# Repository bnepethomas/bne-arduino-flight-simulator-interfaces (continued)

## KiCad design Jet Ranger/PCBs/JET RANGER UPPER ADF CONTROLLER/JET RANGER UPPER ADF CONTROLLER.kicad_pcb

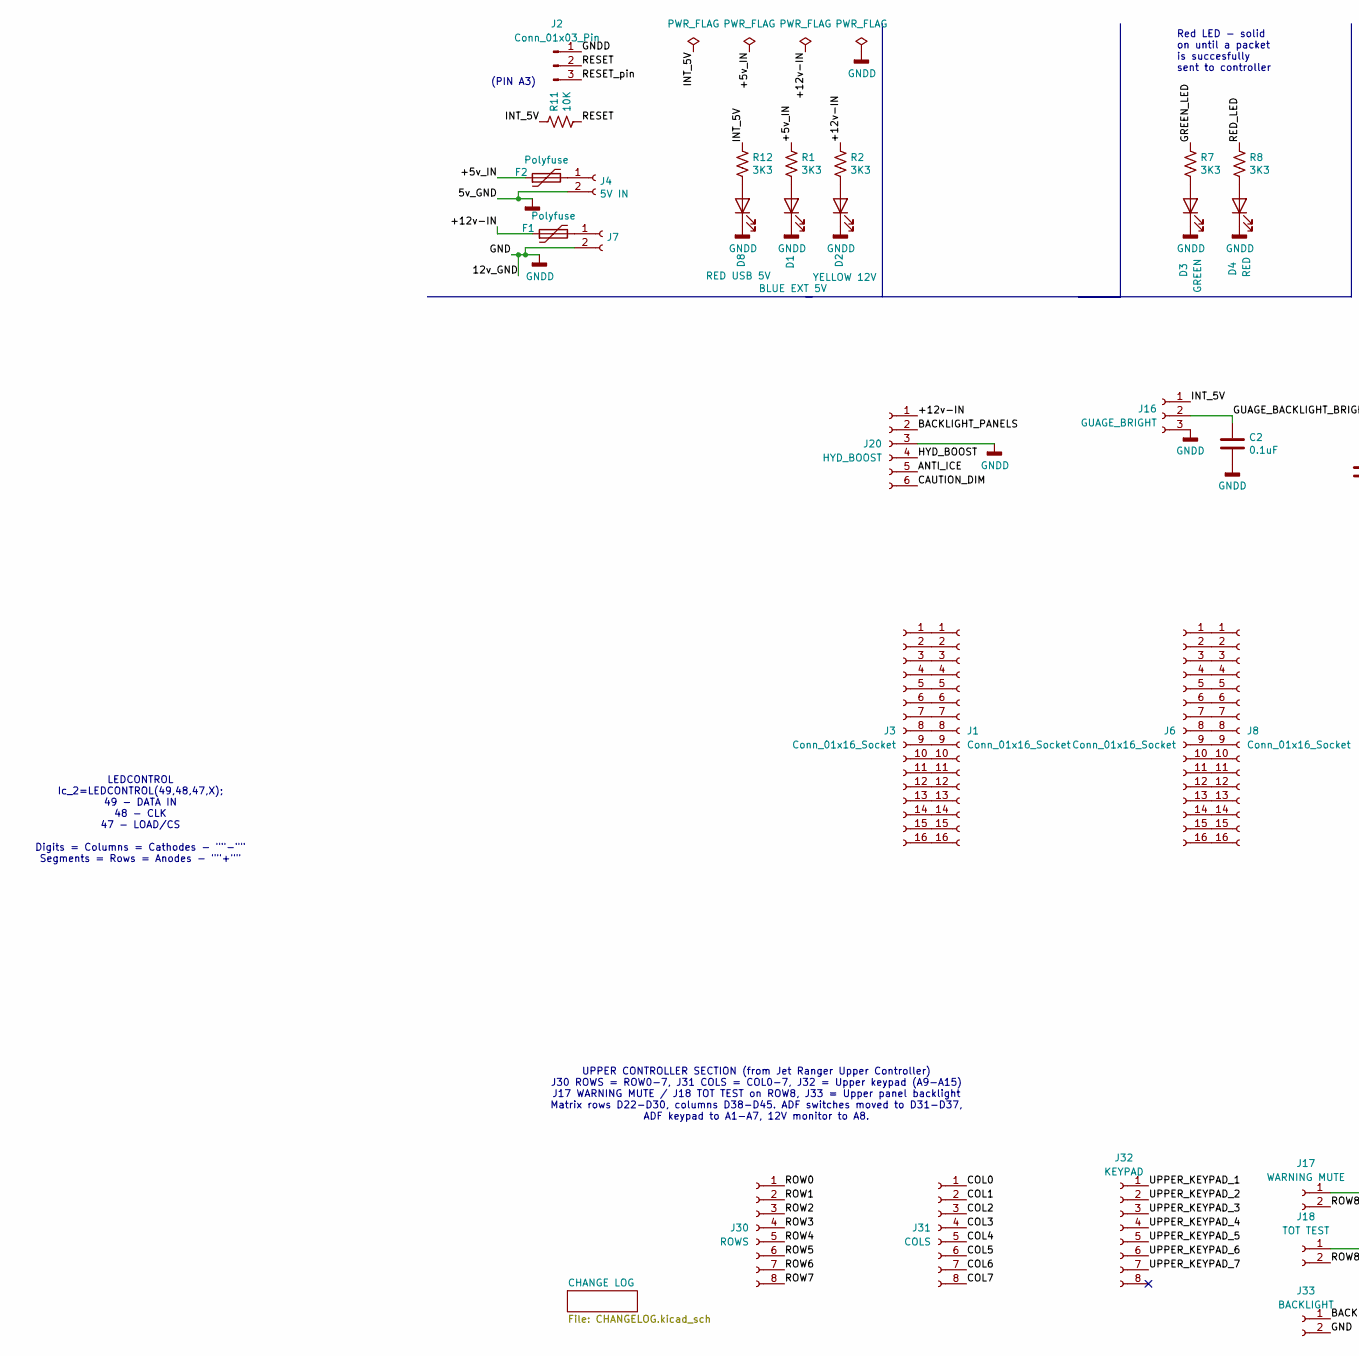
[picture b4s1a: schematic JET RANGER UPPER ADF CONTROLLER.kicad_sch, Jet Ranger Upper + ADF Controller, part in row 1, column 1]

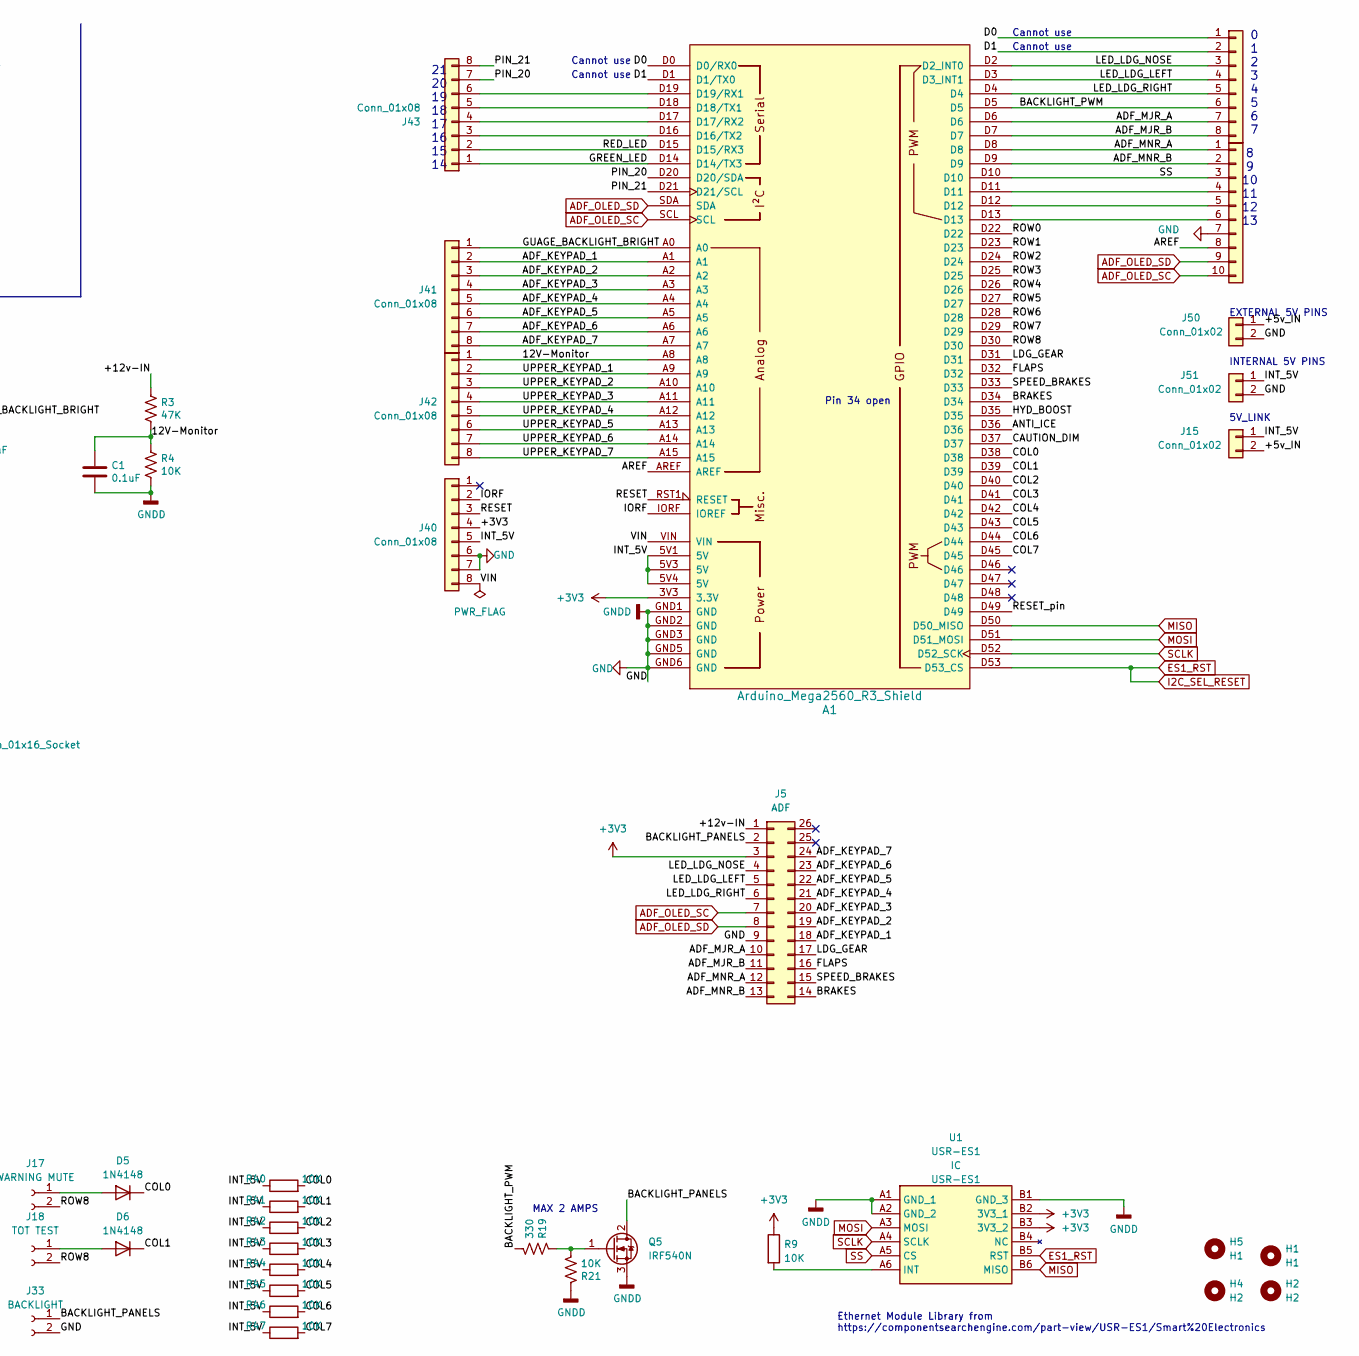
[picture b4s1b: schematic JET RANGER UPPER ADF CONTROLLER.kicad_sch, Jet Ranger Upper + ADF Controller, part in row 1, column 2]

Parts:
A1: Arduino_Mega2560_R3_Shield
C1, C2: 0.1uF; C_Disc_D6.0mm_W2.5mm_P5.00mm
D1: BLUE EXT 5V; LED_D3.0mm
D2: YELLOW 12V; LED_D3.0mm
D3: GREEN; LED_D3.0mm
D4: RED; LED_D3.0mm
D5, D6: 1N4148; D_DO-35_SOD27_P7.62mm_Horizontal
D8: RED USB 5V; LED_D3.0mm
F1, F2: Polyfuse; Fuse_Littelfuse_395Series
H1, H5: H1; MountingHole_3.2mm_M3
H2, H4: H2; MountingHole_3.2mm_M3
J1, J3, J6, J8: Conn_01x16_Socket; PinHeader_1x16_P2.54mm_Vertical
J2: Conn_01x03_Pin; PinHeader_1x03_P2.54mm_Vertical
J4: 5V IN; BarrelJack_Horizontal
J5: ADF; IDC-Header_2x13_P2.54mm_Vertical
J7: STEPPER IN 12-20VDC; BarrelJack_Horizontal
J15, J50, J51: Conn_01x02; PinHeader_1x02_P2.54mm_Vertical
J16: GUAGE_BRIGHT; Molex_KK-254_AE-6410-03A_1x03_P2.54mm_Vertical
J17: WARNING MUTE; Molex_KK-254_AE-6410-02A_1x02_P2.54mm_Vertical
J18: TOT TEST; Molex_KK-254_AE-6410-02A_1x02_P2.54mm_Vertical
J20: HYD_BOOST; Molex_KK-254_AE-6410-06A_1x06_P2.54mm_Vertical
J30: ROWS; Molex_KK-254_AE-6410-08A_1x08_P2.54mm_Vertical
J31: COLS; Molex_KK-254_AE-6410-08A_1x08_P2.54mm_Vertical
J32: KEYPAD; Molex_KK-254_AE-6410-08A_1x08_P2.54mm_Vertical
J33: BACKLIGHT; Molex_KK-254_AE-6410-02A_1x02_P2.54mm_Vertical
J40, J41, J42, J43, J44: Conn_01x08; PinHeader_1x08_P2.54mm_Vertical
J45: Conn_01x10; PinHeader_1x10_P2.54mm_Vertical
Q5: IRF540N; TO-220-3_Vertical
R1, R2, R7, R8, R12: 3K3; R_Axial_DIN0207_L6.3mm_D2.5mm_P2.54mm_Vertical
R3: 47K; R_Axial_DIN0207_L6.3mm_D2.5mm_P2.54mm_Vertical
R4, R9, R11, R21, R40, R41, R42, R43, R44, R45, R46, R47: 10K; R_Axial_DIN0207_L6.3mm_D2.5mm_P2.54mm_Vertical
R19: 330; R_Axial_DIN0207_L6.3mm_D2.5mm_P2.54mm_Vertical
U1: USR-ES1; USRES1; Manufacturer_Part_Number USR-ES1

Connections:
+3V3: A1.3V3 (3.3V), J5.3, J40.4, R9.1, U1.B2 (3V3_1), U1.B3 (3V3_2)
/12V-Monitor: A1.A8, C1.1, J42.1, R3.2, R4.1
/+5v_IN: F2.1, J15.2, J50.1, R1.1
/+12v-IN: F1.1, J5.1, J20.1, R2.1, R3.1
/ADF_KEYPAD_1: A1.A1, J5.18, J41.2
/ADF_KEYPAD_2: A1.A2, J5.19, J41.3
/ADF_KEYPAD_3: A1.A3, J5.20, J41.4
/ADF_KEYPAD_4: A1.A4, J5.21, J41.5
/ADF_KEYPAD_5: A1.A5, J5.22, J41.6
/ADF_KEYPAD_6: A1.A6, J5.23, J41.7
/ADF_KEYPAD_7: A1.A7, J5.24, J41.8
/ADF_MJR_A: A1.D6, J5.10, J44.7
/ADF_MJR_B: A1.D7, J5.11, J44.8
/ADF_MNR_A: A1.D8, J5.12, J45.1
/ADF_MNR_B: A1.D9, J5.13, J45.2
/ANTI_ICE: A1.D36, J20.5
/AREF: A1.AREF, J45.8
/BACKLIGHT_PANELS: J5.2, J20.2, J33.1, Q5.2 (D)
/BACKLIGHT_PWM: A1.D5, J44.6, R19.2
/BRAKES: A1.D34, J5.14
/CAUTION_DIM: A1.D37, J20.6
/COL0: A1.D38, D5.1 (K), J31.1, R40.2
/COL1: A1.D39, D6.1 (K), J31.2, R41.2
/COL2: A1.D40, J31.3, R42.2
/COL3: A1.D41, J31.4, R43.2
/COL4: A1.D42, J31.5, R44.2
/COL5: A1.D43, J31.6, R45.2
/COL6: A1.D44, J31.7, R46.2
/COL7: A1.D45, J31.8, R47.2
/D0: A1.D0 (D0/RX0), J44.1
/D1: A1.D1 (D1/TX0), J44.2
/FLAPS: A1.D32, J5.16
/GREEN_LED: A1.D14 (D14/TX3), J43.1, R7.1
/GUAGE_BACKLIGHT_BRIGHT: A1.A0, C2.1, J16.2, J41.1
/HYD_BOOST: A1.D35, J20.4
/INT_5V: A1.5V1 (5V), A1.5V3 (5V), A1.5V4 (5V), J15.1, J16.1, J40.5, J51.1, R11.1, R12.1, R40.1, R41.1, R42.1, R43.1, R44.1, R45.1, R46.1, R47.1
/IORF: A1.IORF (IOREF), J40.2
/LDG_GEAR: A1.D31, J5.17
/LED_LDG_LEFT: A1.D3 (D3_INT1), J5.5, J44.4
/LED_LDG_NOSE: A1.D2 (D2_INT0), J5.4, J44.3
/LED_LDG_RIGHT: A1.D4, J5.6, J44.5
/PIN_20: A1.D20 (D20/SDA), J43.7
/PIN_21: A1.D21 (D21/SCL), J43.8
/RED_LED: A1.D15 (D15/RX3), J43.2, R8.1
/RESET: A1.RST1 (RESET), J2.2, J40.3, R11.2
/RESET_pin: A1.D49, J2.3
/ROW0: A1.D22, J30.1
/ROW1: A1.D23, J30.2
/ROW2: A1.D24, J30.3
/ROW3: A1.D25, J30.4
/ROW4: A1.D26, J30.5
/ROW5: A1.D27, J30.6
/ROW6: A1.D28, J30.7
/ROW7: A1.D29, J30.8
/ROW8: A1.D30, J17.2, J18.2
/SPEED_BRAKES: A1.D33, J5.15
/UPPER_KEYPAD_1: A1.A9, J32.1, J42.2
/UPPER_KEYPAD_2: A1.A10, J32.2, J42.3
/UPPER_KEYPAD_3: A1.A11, J32.3, J42.4
/UPPER_KEYPAD_4: A1.A12, J32.4, J42.5
/UPPER_KEYPAD_5: A1.A13, J32.5, J42.6
/UPPER_KEYPAD_6: A1.A14, J32.6, J42.7
/UPPER_KEYPAD_7: A1.A15, J32.7, J42.8
/VIN: A1.VIN, J40.8
ADF_OLED_SC: A1.SCL, J5.7, J45.10
ADF_OLED_SD: A1.SDA, J5.8, J45.9
ES1_RST: A1.D53 (D53_CS), U1.B5 (RST)
GND: A1.GND1 (GND), A1.GND2 (GND), A1.GND3 (GND), A1.GND5 (GND), A1.GND6 (GND), C1.2, C2.2, D1.1 (K), D2.1 (K), D3.1 (K), D4.1 (K), D8.1 (K), J2.1, J4.2, J5.9, J7.2, J16.3, J20.3, J33.2, J40.6, J40.7, J45.7, J50.2, J51.2, Q5.3 (S), R4.2, R21.1, U1.A1 (GND_1), U1.A2 (GND_2), U1.B1 (GND_3)
MISO: A1.D50 (D50_MISO), U1.B6 (MISO)
MOSI: A1.D51 (D51_MOSI), U1.A3 (MOSI)
unnamed: A1.D16 (D16/TX2), J43.3
unnamed: A1.D17 (D17/RX2), J43.4
unnamed: A1.D18 (D18/TX1), J43.5
unnamed: A1.D19 (D19/RX1), J43.6
unnamed: D1.2 (A), R1.2
unnamed: D2.2 (A), R2.2
unnamed: D3.2 (A), R7.2
unnamed: D4.2 (A), R8.2
unnamed: D5.2 (A), J17.1
unnamed: D6.2 (A), J18.1
unnamed: D8.2 (A), R12.2
unnamed: J1.1, J3.1
unnamed: J1.2, J3.2
unnamed: J1.3, J3.3
unnamed: J1.4, J3.4
unnamed: J1.5, J3.5
unnamed: J1.6, J3.6
unnamed: J1.7, J3.7
unnamed: J1.8, J3.8
unnamed: J1.9, J3.9
unnamed: J1.10, J3.10
unnamed: J1.11, J3.11
unnamed: J1.12, J3.12
unnamed: J1.13, J3.13
unnamed: J1.14, J3.14
unnamed: J1.15, J3.15
unnamed: J1.16, J3.16
unnamed: F2.2, J4.1
unnamed: J6.1, J8.1
unnamed: J6.2, J8.2
unnamed: J6.3, J8.3
unnamed: J6.4, J8.4
unnamed: J6.5, J8.5
unnamed: J6.6, J8.6
unnamed: J6.7, J8.7
unnamed: J6.8, J8.8
unnamed: J6.9, J8.9
unnamed: J6.10, J8.10
unnamed: J6.11, J8.11
unnamed: J6.12, J8.12
unnamed: J6.13, J8.13
unnamed: J6.14, J8.14
unnamed: J6.15, J8.15
unnamed: J6.16, J8.16
unnamed: F1.2, J7.1
unnamed: A1.D11, J45.4
unnamed: A1.D12, J45.5
unnamed: A1.D13, J45.6
unnamed: Q5.1 (G), R19.1, R21.2
unnamed: R9.2, U1.A6 (INT)
SCLK: A1.D52 (D52_SCK), U1.A4 (SCLK)
SS: A1.D10, J45.3, U1.A5 (CS)

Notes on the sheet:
Pin 34 open
MAX 2 AMPS
INTERNAL 5V PINS
Ethernet Module Library from https://componentsearchengine.com/part-view/USR-ES1/Smart%20Electronics
Cannot use
(PIN A3)
0 1 2 3 4 5 6 7
LEDCONTROL Ic_2=LEDCONTROL(49,48,47,X); 49 - DATA IN 48 - CLK 47 - LOAD/CS Digits = Columns = Cathodes - ""-"" Segments = Rows = Anodes - ""+""
Red LED - solid on until a packet is succesfully sent to controller
5V_LINK
21 20 19 18 17 16 15 14
EXTERNAL 5V PINS
8 9 10 11 12 13
UPPER CONTROLLER SECTION (from Jet Ranger Upper Controller) J30 ROWS = ROW0-7, J31 COLS = COL0-7, J32 = Upper keypad (A9-A15) J17 WARNING MUTE / J18 TOT TEST on ROW8, J33 = Upper panel backlight Matrix rows D22-D30, columns D38-D45. ADF switches moved to D31-D37, ADF keypad to A1-A7, 12V monitor to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

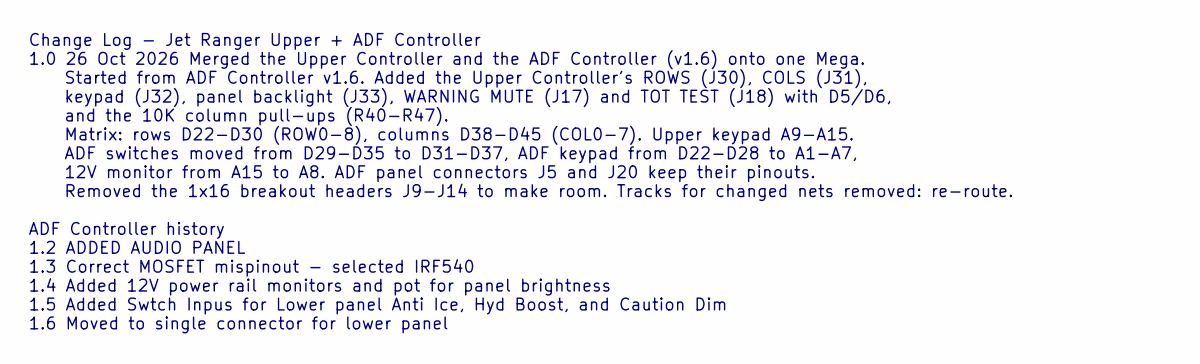
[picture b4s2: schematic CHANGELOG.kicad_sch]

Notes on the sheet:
Change Log - Jet Ranger Upper + ADF Controller 1.0 26 Oct 2026 Merged the Upper Controller and the ADF Controller (v1.6) onto one Mega. Started from ADF Controller v1.6. Added the Upper Controller's ROWS (J30), COLS (J31), keypad (J32), panel backlight (J33), WARNING MUTE (J17) and TOT TEST (J18) w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

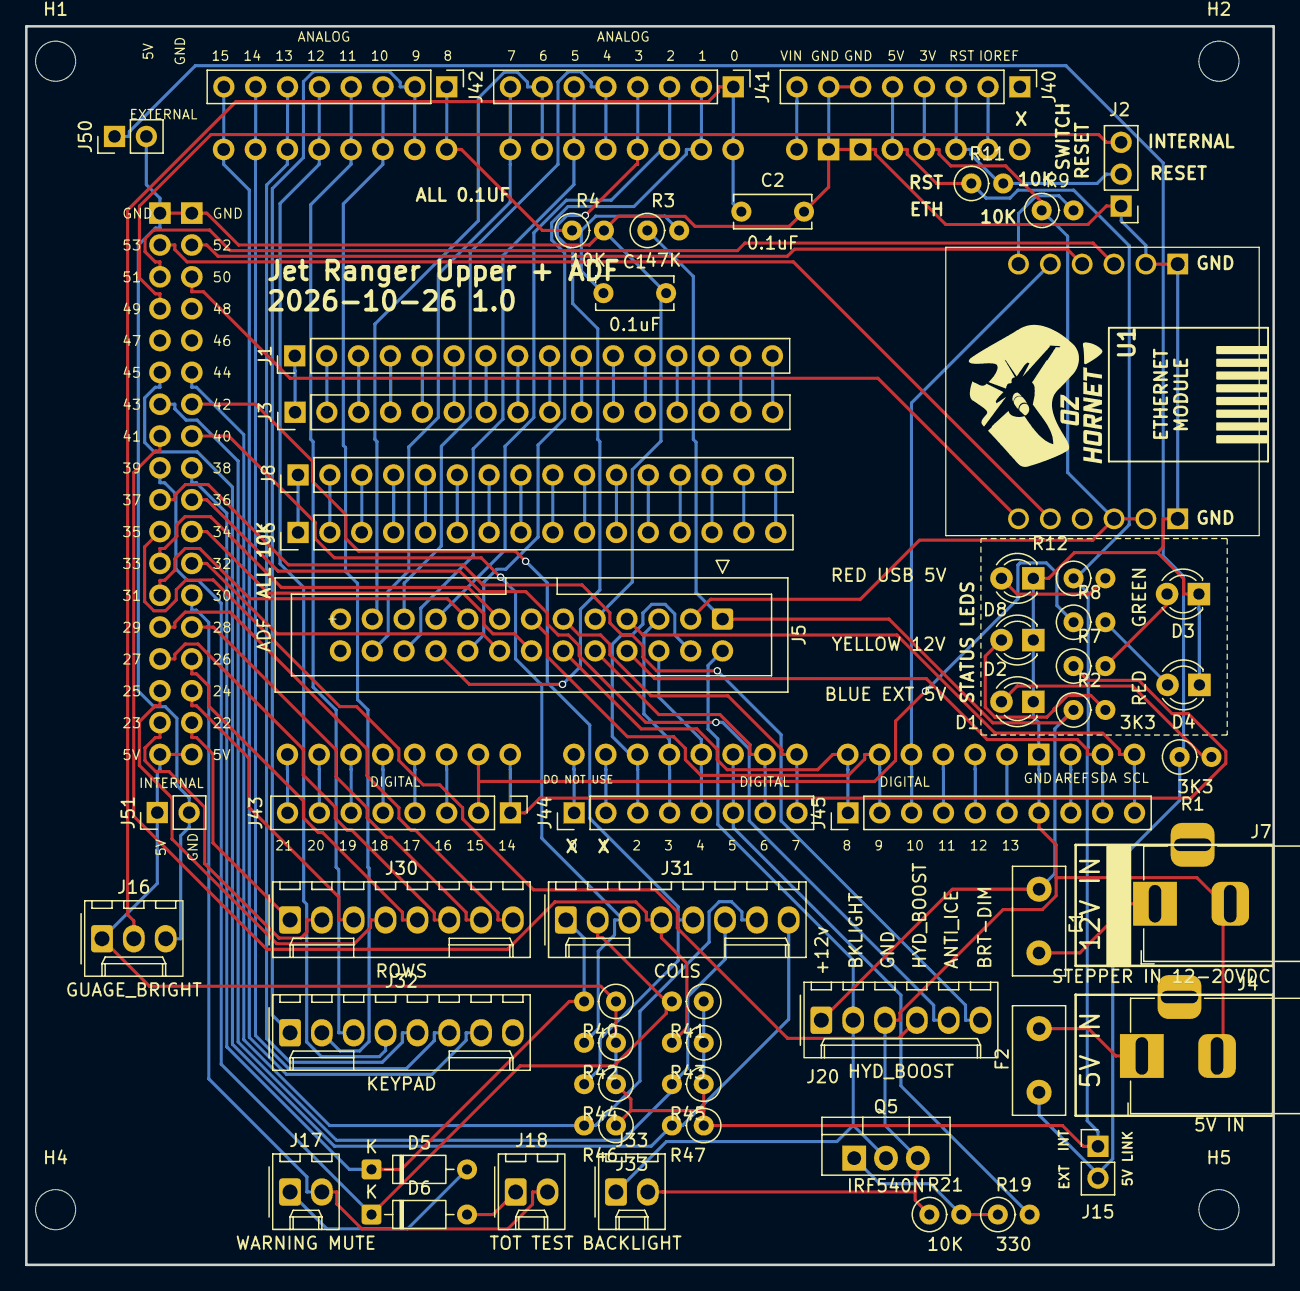
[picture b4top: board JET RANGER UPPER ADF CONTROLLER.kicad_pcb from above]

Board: 2 copper layers, 99.5 x 98.8 mm, 62 parts (0 on the bottom side), 122 nets.

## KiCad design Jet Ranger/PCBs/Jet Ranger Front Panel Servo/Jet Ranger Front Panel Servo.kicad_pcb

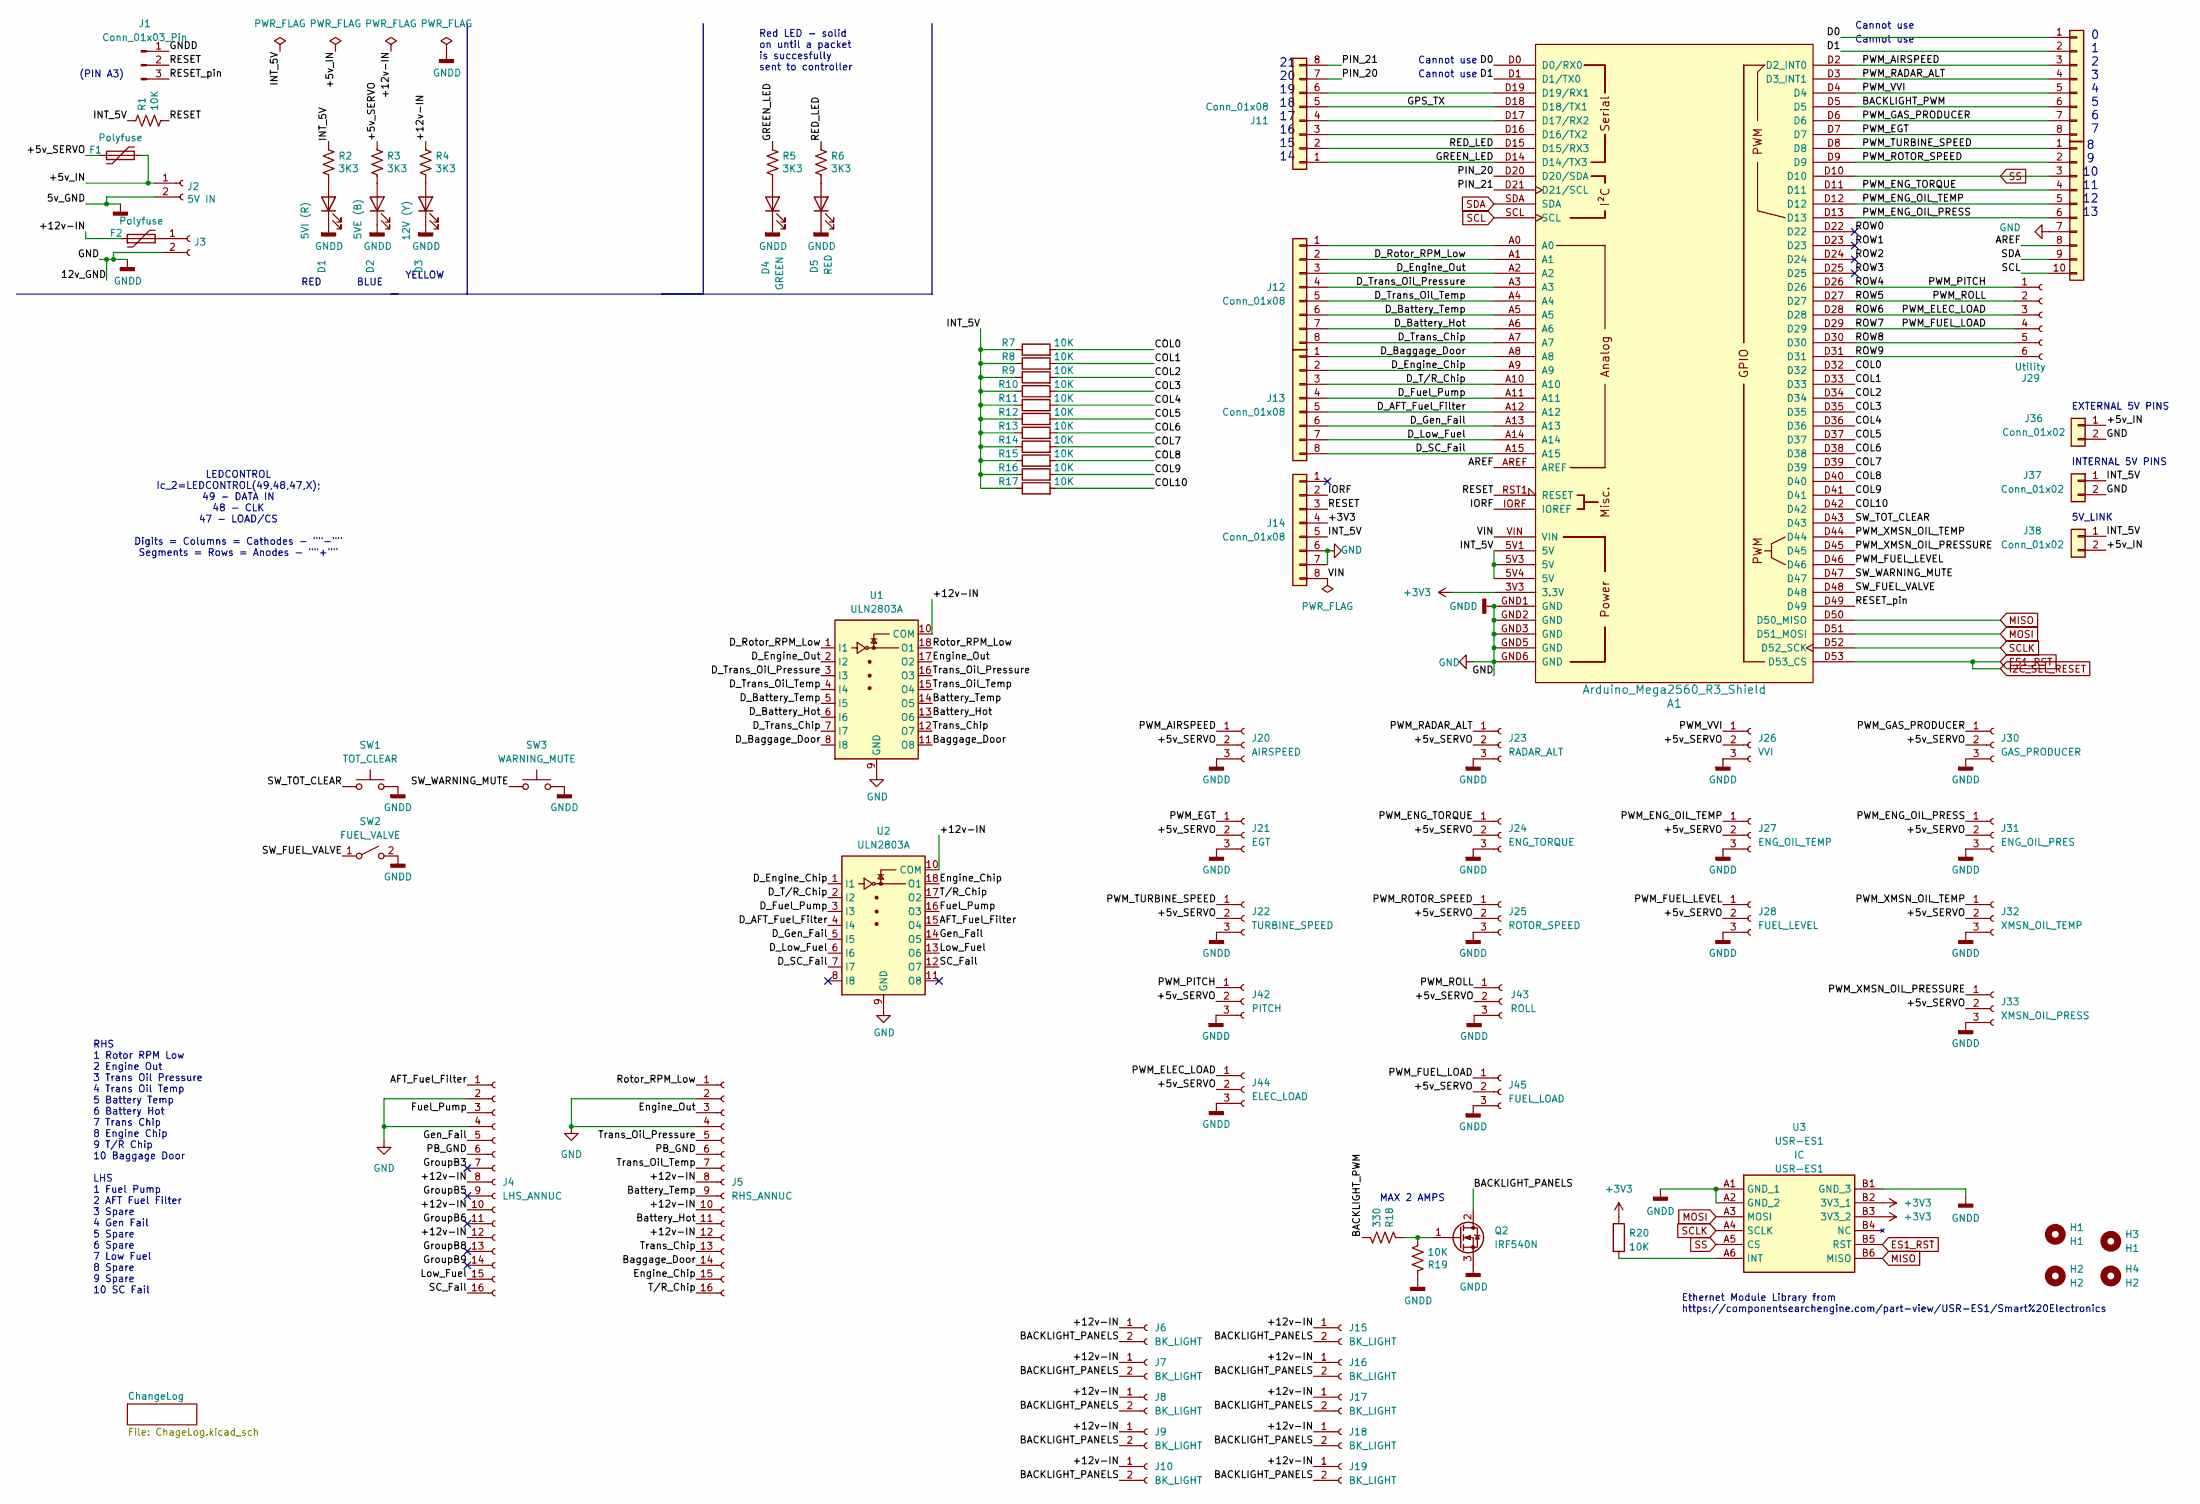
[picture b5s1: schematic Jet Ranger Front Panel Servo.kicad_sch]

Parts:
A1: Arduino_Mega2560_R3_Shield
D1: 5VI (R); LED_D3.0mm
D2: 5VE (B); LED_D3.0mm
D3: 12V (Y); LED_D3.0mm
D4: GREEN; LED_D3.0mm
D5: RED; LED_D3.0mm
F1, F2: Polyfuse; Fuse_Littelfuse_395Series
H1, H3: H1; MountingHole_3.2mm_M3
H2, H4: H2; MountingHole_3.2mm_M3
J1: Conn_01x03_Pin; PinHeader_1x03_P2.54mm_Vertical
J2: 5V IN; BarrelJack_Horizontal
J3: STEPPER IN 12-20VDC; BarrelJack_Horizontal
J4: LHS_ANNUC; IDC-Header_2x08_P2.54mm_Vertical
J5: RHS_ANNUC; IDC-Header_2x08_P2.54mm_Vertical
J6, J7, J8, J9, J10, J15, J16, J17, J18, J19: BK_LIGHT; Molex_KK-254_AE-6410-02A_1x02_P2.54mm_Vertical
J11, J12, J13, J14, J34: Conn_01x08; PinHeader_1x08_P2.54mm_Vertical
J20: AIRSPEED; PinHeader_1x03_P2.54mm_Vertical
J21: EGT; PinHeader_1x03_P2.54mm_Vertical
J22: TURBINE_SPEED; PinHeader_1x03_P2.54mm_Vertical
J23: RADAR_ALT; PinHeader_1x03_P2.54mm_Vertical
J24: ENG_TORQUE; PinHeader_1x03_P2.54mm_Vertical
J25: ROTOR_SPEED; PinHeader_1x03_P2.54mm_Vertical
J26: VVI; PinHeader_1x03_P2.54mm_Vertical
J27: ENG_OIL_TEMP; PinHeader_1x03_P2.54mm_Vertical
J28: FUEL_LEVEL; PinHeader_1x03_P2.54mm_Vertical
J29: Utility; PinHeader_1x06_P2.54mm_Vertical
J30: GAS_PRODUCER; PinHeader_1x03_P2.54mm_Vertical
J31: ENG_OIL_PRES; PinHeader_1x03_P2.54mm_Vertical
J32: XMSN_OIL_TEMP; PinHeader_1x03_P2.54mm_Vertical
J33: XMSN_OIL_PRESS; PinHeader_1x03_P2.54mm_Vertical
J35: Conn_01x10; PinHeader_1x10_P2.54mm_Vertical
J36, J37, J38: Conn_01x02; PinHeader_1x02_P2.54mm_Vertical
J42: PITCH; PinHeader_1x03_P2.54mm_Vertical
J43: ROLL; PinHeader_1x03_P2.54mm_Vertical
J44: ELEC_LOAD; PinHeader_1x03_P2.54mm_Vertical
J45: FUEL_LOAD; PinHeader_1x03_P2.54mm_Vertical
Q2: IRF540N; TO-220-3_Vertical
R1, R7, R8, R9, R10, R11, R12, R13, R14, R15, R16, R17, R19, R20: 10K; R_Axial_DIN0207_L6.3mm_D2.5mm_P2.54mm_Vertical
R2, R3, R4, R5, R6: 3K3; R_Axial_DIN0207_L6.3mm_D2.5mm_P2.54mm_Vertical
R18: 330; R_Axial_DIN0207_L6.3mm_D2.5mm_P2.54mm_Vertical
SW1: TOT_CLEAR; Molex_KK-254_AE-6410-02A_1x02_P2.54mm_Vertical
SW2: FUEL_VALVE; Molex_KK-254_AE-6410-02A_1x02_P2.54mm_Vertical
SW3: WARNING_MUTE; Molex_KK-254_AE-6410-02A_1x02_P2.54mm_Vertical
U1, U2: ULN2803A; DIP-18_W7.62mm
U3: USR-ES1; USRES1; Manufacturer_Part_Number USR-ES1

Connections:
+3V3: A1.3V3 (3.3V), J14.4, R20.1, U3.B2 (3V3_1), U3.B3 (3V3_2)
/+5v_IN: F1.2, J2.1, J36.1, J38.2
/+5v_SERVO: F1.1, J20.2, J21.2, J22.2, J23.2, J24.2, J25.2, J26.2, J27.2, J28.2, J30.2, J31.2, J32.2, J33.2, J42.2, J43.2, J44.2, J45.2, R3.1
/+12v-IN: F2.1, J4.8, J4.10, J4.12, J5.8, J5.10, J5.12, J6.1, J7.1, J8.1, J9.1, J10.1, J15.1, J16.1, J17.1, J18.1, J19.1, R4.1, U1.10 (COM), U2.10 (COM)
/AFT_Fuel_Filter: J4.1, U2.15 (O4)
/AREF: A1.AREF, J35.8
/BACKLIGHT_PANELS: J6.2, J7.2, J8.2, J9.2, J10.2, J15.2, J16.2, J17.2, J18.2, J19.2, Q2.2 (D)
/BACKLIGHT_PWM: A1.D5, J34.6, R18.2
/Baggage_Door: J5.14, U1.11 (O8)
/Battery_Hot: J5.11, U1.13 (O6)
/Battery_Temp: J5.9, U1.14 (O5)
/COL0: A1.D32, R7.2
/COL1: A1.D33, R8.2
/COL2: A1.D34, R9.2
/COL3: A1.D35, R10.2
/COL4: A1.D36, R11.2
/COL5: A1.D37, R12.2
/COL6: A1.D38, R13.2
/COL7: A1.D39, R14.2
/COL8: A1.D40, R15.2
/COL9: A1.D41, R16.2
/COL10: A1.D42, R17.2
/D0: A1.D0 (D0/RX0), J34.1
/D1: A1.D1 (D1/TX0), J34.2
/D_AFT_Fuel_Filter: A1.A12, J13.5, U2.4 (I4)
/D_Baggage_Door: A1.A8, J13.1, U1.8 (I8)
/D_Battery_Hot: A1.A6, J12.7, U1.6 (I6)
/D_Battery_Temp: A1.A5, J12.6, U1.5 (I5)
/D_Engine_Chip: A1.A9, J13.2, U2.1 (I1)
/D_Engine_Out: A1.A2, J12.3, U1.2 (I2)
/D_Fuel_Pump: A1.A11, J13.4, U2.3 (I3)
/D_Gen_Fail: A1.A13, J13.6, U2.5 (I5)
/D_Low_Fuel: A1.A14, J13.7, U2.6 (I6)
/D_Rotor_RPM_Low: A1.A1, J12.2, U1.1 (I1)
/D_SC_Fail: A1.A15, J13.8, U2.7 (I7)
/D_Trans_Chip: A1.A7, J12.8, U1.7 (I7)
/D_Trans_Oil_Pressure: A1.A3, J12.4, U1.3 (I3)
/D_Trans_Oil_Temp: A1.A4, J12.5, U1.4 (I4)
/D_T/R_Chip: A1.A10, J13.3, U2.2 (I2)
/Engine_Chip: J5.15, U2.18 (O1)
/Engine_Out: J5.3, U1.17 (O2)
/Fuel_Pump: J4.3, U2.16 (O3)
/GPS_TX: A1.D18 (D18/TX1), J11.5
/GREEN_LED: A1.D14 (D14/TX3), J11.1, R5.1
/Gen_Fail: J4.5, U2.14 (O5)
/GroupB3: J4.7
/GroupB5: J4.9
/GroupB6: J4.11
/GroupB8: J4.13
/GroupB9: J4.14
/INT_5V: A1.5V1 (5V), A1.5V3 (5V), A1.5V4 (5V), J14.5, J37.1, J38.1, R1.1, R2.1, R7.1, R8.1, R9.1, R10.1, R11.1, R12.1, R13.1, R14.1, R15.1, R16.1, R17.1
/IORF: A1.IORF (IOREF), J14.2
/Low_Fuel: J4.15, U2.13 (O6)
/PB_GND: J4.6, J5.6
/PIN_20: A1.D20 (D20/SDA), J11.7
/PIN_21: A1.D21 (D21/SCL), J11.8
/PWM_AIRSPEED: A1.D2 (D2_INT0), J20.1, J34.3
/PWM_EGT: A1.D7, J21.1, J34.8
/PWM_ELEC_LOAD: A1.D28, J29.3, J44.1
/PWM_ENG_OIL_PRESS: A1.D13, J31.1, J35.6
/PWM_ENG_OIL_TEMP: A1.D12, J27.1, J35.5
/PWM_ENG_TORQUE: A1.D11, J24.1, J35.4
/PWM_FUEL_LEVEL: A1.D46, J28.1
/PWM_FUEL_LOAD: A1.D29, J29.4, J45.1
/PWM_GAS_PRODUCER: A1.D6, J30.1, J34.7
/PWM_PITCH: A1.D26, J29.1, J42.1
/PWM_RADAR_ALT: A1.D3 (D3_INT1), J23.1, J34.4
/PWM_ROLL: A1.D27, J29.2, J43.1
/PWM_ROTOR_SPEED: A1.D9, J25.1, J35.2
/PWM_TURBINE_SPEED: A1.D8, J22.1, J35.1
/PWM_VVI: A1.D4, J26.1, J34.5
/PWM_XMSN_OIL_PRESSURE: A1.D45, J33.1
/PWM_XMSN_OIL_TEMP: A1.D44, J32.1
/RED_LED: A1.D15 (D15/RX3), J11.2, R6.1
/RESET: A1.RST1 (RESET), J1.2, J14.3, R1.2
/RESET_pin: A1.D49, J1.3
/ROW0: A1.D22
/ROW1: A1.D23
/ROW2: A1.D24
/ROW3: A1.D25
/ROW8: A1.D30, J29.5
/ROW9: A1.D31, J29.6
/Rotor_RPM_Low: J5.1, U1.18 (O1)
/SC_Fail: J4.16, U2.12 (O7)
/SW_FUEL_VALVE: A1.D48, SW2.1 (A)
/SW_TOT_CLEAR: A1.D43, SW1.1
/SW_WARNING_MUTE: A1.D47, SW3.1
/Trans_Chip: J5.13, U1.12 (O7)
/Trans_Oil_Pressure: J5.5, U1.16 (O3)
/Trans_Oil_Temp: J5.7, U1.15 (O4)
/T/R_Chip: J5.16, U2.17 (O2)
/VIN: A1.VIN, J14.8
ES1_RST: A1.D53 (D53_CS), U3.B5 (RST)
GND: A1.GND1 (GND), A1.GND2 (GND), A1.GND3 (GND), A1.GND5 (GND), A1.GND6 (GND), D1.1 (K), D2.1 (K), D3.1 (K), D4.1 (K), D5.1 (K), J1.1, J2.2, J3.2, J4.2, J4.4, J5.2, J5.4, J14.6, J14.7, J20.3, J21.3, J22.3, J23.3, J24.3, J25.3, J26.3, J27.3, J28.3, J30.3, J31.3, J32.3, J33.3, J35.7, J36.2, J37.2, J42.3, J43.3, J44.3, J45.3, Q2.3 (S), R19.1, SW1.2, SW2.2 (B), SW3.2, U1.9 (GND), U2.9 (GND), U3.A1 (GND_1), U3.A2 (GND_2), U3.B1 (GND_3)
MISO: A1.D50 (D50_MISO), U3.B6 (MISO)
MOSI: A1.D51 (D51_MOSI), U3.A3 (MOSI)
unnamed: A1.D16 (D16/TX2), J11.3
unnamed: A1.D17 (D17/RX2), J11.4
unnamed: A1.D19 (D19/RX1), J11.6
unnamed: D1.2 (A), R2.2
unnamed: D2.2 (A), R3.2
unnamed: D3.2 (A), R4.2
unnamed: D4.2 (A), R5.2
unnamed: D5.2 (A), R6.2
unnamed: F2.2, J3.1
unnamed: A1.A0, J12.1
unnamed: Q2.1 (G), R18.1, R19.2
unnamed: R20.2, U3.A6 (INT)
SCL: A1.SCL, J35.10
SCLK: A1.D52 (D52_SCK), U3.A4 (SCLK)
SDA: A1.SDA, J35.9
SS: A1.D10, J35.3, U3.A5 (CS)

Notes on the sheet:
YELLOW
MAX 2 AMPS
BLUE
INTERNAL 5V PINS
Ethernet Module Library from https://componentsearchengine.com/part-view/USR-ES1/Smart%20Electronics
Cannot use
RED
(PIN A3)
0 1 2 3 4 5 6 7
LEDCONTROL Ic_2=LEDCONTROL(49,48,47,X); 49 - DATA IN 48 - CLK 47 - LOAD/CS Digits = Columns = Cathodes - ""-"" Segments = Rows = Anodes - ""+""
Red LED - solid on until a packet is succesfully sent to controller
RHS 1 Rotor RPM Low 2 Engine Out 3 Trans Oil Pressure 4 Trans Oil Temp 5 Battery Temp 6 Battery Hot 7 Trans Chip 8 Engine Chip 9 T/R Chip 10 Baggage Door LHS 1 Fuel Pump 2 AFT Fuel Filter 3 Spare 4 Gen Fail 5 Spare 6 Spare 7 Low Fuel 8 Spare 9 Spare 10 SC Fail
5V_LINK
21 20 19 18 17 16 15 14
EXTERNAL 5V PINS
8 9 10 11 12 13

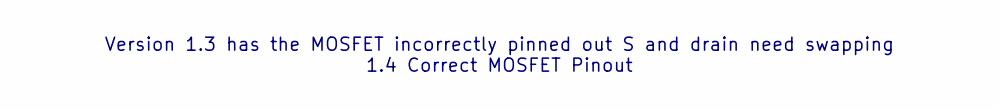
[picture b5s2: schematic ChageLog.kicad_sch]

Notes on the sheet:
Version 1.3 has the MOSFET incorrectly pinned out S and drain need swapping 1.4 Correct MOSFET Pinout

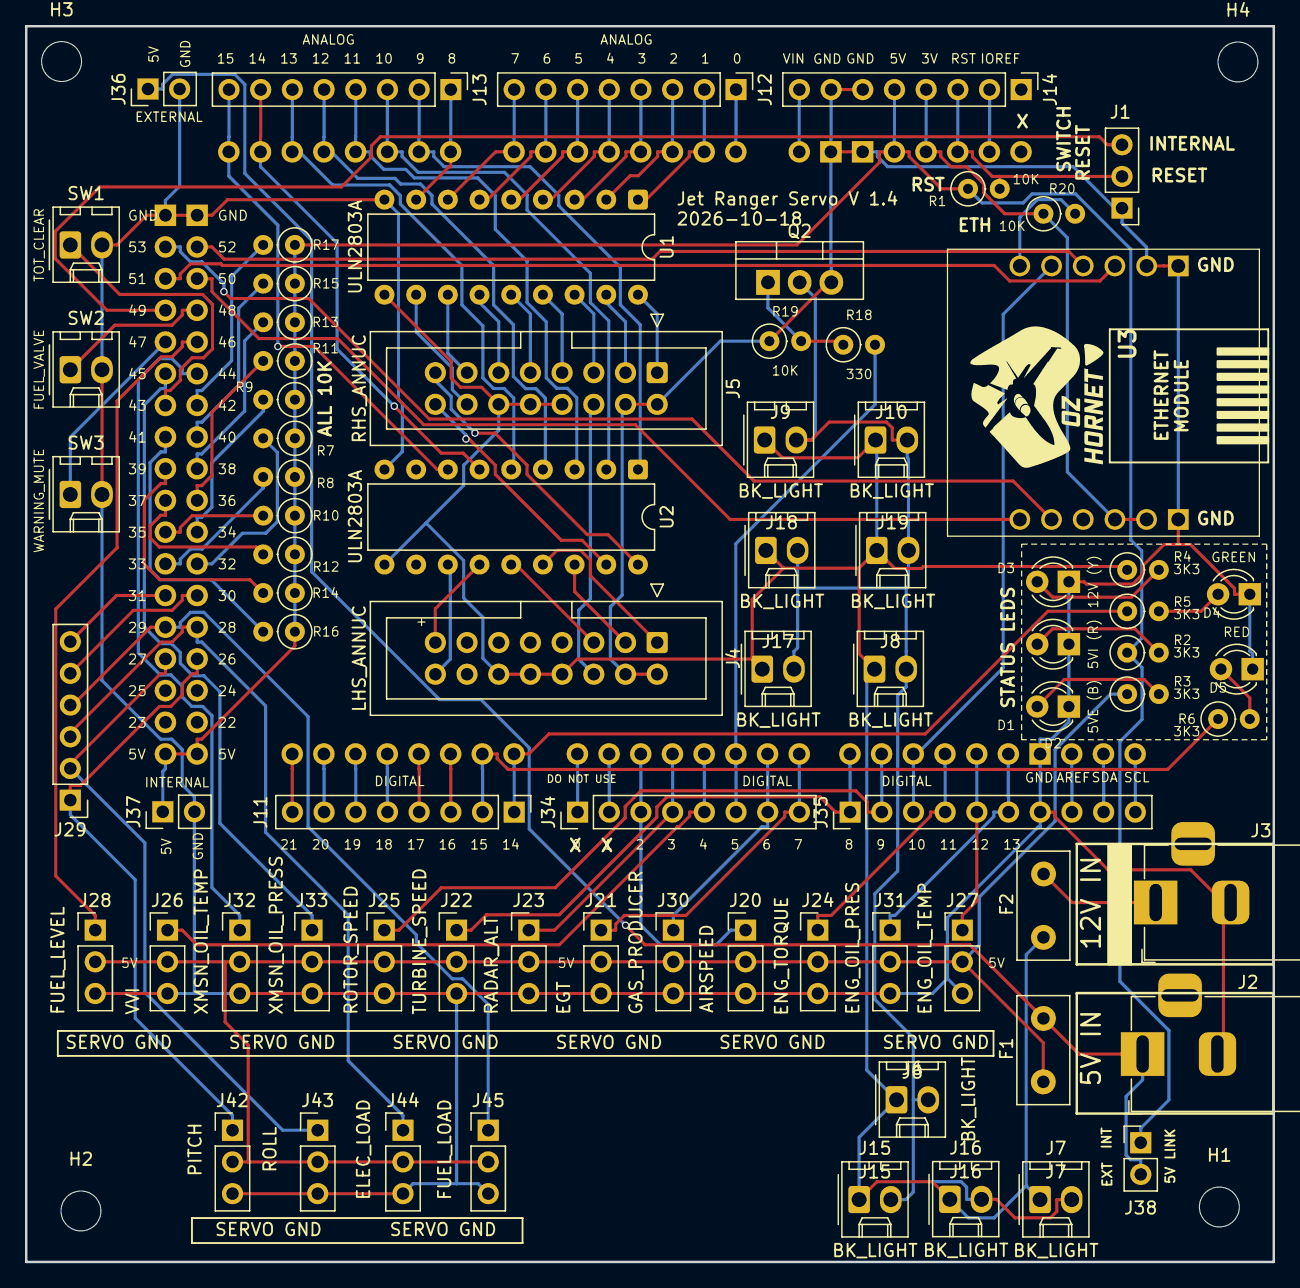
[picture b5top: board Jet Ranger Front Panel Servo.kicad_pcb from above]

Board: 2 copper layers, 100.0 x 99.1 mm, 81 parts (0 on the bottom side), 103 nets.

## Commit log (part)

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2026-01-26 c# most of Jet Ranger base values set - need to work on radios
2026-01-27 comm is working
2026-01-28 Due Prodcution Controller
2026-01-28 jet ranger
2026-01-28 due pcb update
2026-01-29 due controller
2026-01-29 controller
2026-01-29 DUE Prod
2026-01-30 encoder
2026-01-30 Radio controller working with Mega
2026-01-31 displays updating correctly
2026-02-01 added UDP listener
2026-02-01 before .net migration
2026-02-01 Arduin Now Sending COM1 Stand by to MSFS
2026-02-01 PCB UPDATE
2026-02-02 radio controller push button framework
2026-02-03 progressing on swap
2026-02-03 comm swap working
2026-02-03 comm work
2026-02-06 Handling UDP from MSFS
2026-02-06 COM1 frequencies now working
2026-02-06 comm1 and 2
2026-02-07 timing adjusted
2026-02-07 battery switch no longer working
2026-02-07 Battery Monitoring working bt Avionics isn't
    After tinkeirng with Event Var and perhaps a logic mistake in event handling
2026-02-07 Main Bus working - unsure why Avionics bus isn't working
    Need to looked at BCD encoding for 5KHz radio spacing
2026-02-07 Voltages now nderstood
    To do Set Frequency using string
2026-02-07 Working with needing BCD for Radios
2026-02-07 Radios working and added Monitoring Applicaiotn
2026-02-08 comms workings frequency non-BCD
    Unable to set Garmin 1000 buttons - need to research if FSUIPC with WASM may be able to solve
2026-02-08 C# side of front panel largely done
2026-02-08 power pcbs with aliexpress connector
2026-02-08 updating Servos
2026-02-09 Indicators
2026-02-10 servo range build out
2026-02-11 gauges
2026-02-12 Servo
    Torque is jittering after attach
2026-02-12 Update JET_RANGER_SERVO_CONTROLLER.ino
    Fixed Servo Jitter be checking for incoming packets every so many mS instead of everytime through the loop
2026-02-13 Servo Test Framework
2026-02-14 Servo Tuner Operational
2026-02-14 Servo work
2026-02-14 Servos
2026-02-14 framework may be working
2026-02-14 Torque is now operational
    Whoot
2026-02-14 working on airspeed
2026-02-15 new c# Project target c# 10
2026-02-15 closed
2026-02-15 airspeed working
2026-02-15 Rotor and Engine RPM
2026-02-15 Fuel Qantity
2026-02-15 Fuel Gauge
2026-02-15 VSI Gauge
2026-02-15 Working on Eng Oil Temp and Pressure gauges not moving
2026-02-15 working on XMSN and need to complete Eng and XSMN in sender
2026-02-16 Bank and Pitch to do
2026-02-16 Roll anbd Bank compelte
    to do
    build new PCB
    Elec load, Fuel Loan Gas Producer Radar Alt
2026-02-20 Fuel & Elec Load, Gas P start dev
2026-02-20 TUNER AND MEGA COMPLETE - NEED TO GET VALUES FROM MSFS
2026-02-21 light test routine ok - now need to develop logic
2026-02-21 working on ITT values
2026-02-21 to fix pitch and roll
2026-02-21 still have a few gauges to align and perhaps add calls to
2026-02-21 Engine out and Rotor Low Warnings now ok
    Needed to compare string not numeric
2026-02-21 troubleshooting gauges
    discovered transmission is deprecated in SimConnect
2026-02-24 comm1 working comm2 and nav1 known bad
2026-02-26 COMMNAV
2026-02-28 rolling minor digit
2026-03-01 Update JET_RANGER_RADIO_CONTROLLER.ino
    Nav Minors need to fix rolling over 990
2026-03-02 Update JET_RANGER_RADIO_CONTROLLER.ino
    Minor Encoders now rolling - todo SimConnect interface for Com2 and Nav
2026-04-26 CrossPlatform First cut
2026-04-26 Cross Platform - compiled and executed
2026-05-04 multi-platform
2026-05-09 retired old input controller
2026-05-10 shorten A
2026-05-10 short2
2026-05-10 shorten3
2026-05-10 shorten4
2026-05-10 shorten5
2026-05-10 Hornet Health Monitor
2026-05-10 Create insert for keepalive
2026-05-11 keepalive added to current boards
2026-05-13 Health Monitor
2026-05-15 MHornetHealthMonitor
2026-05-15 health
2026-05-16 sim control
2026-05-16 right sim control
2026-05-17 Mostly working
2026-05-17 compass
2026-05-18 simcontrol
2026-05-22 left and right lighting
2026-05-24 potentiometer update
2026-05-31 keystrokes and lua
2026-06-07 Backlighting
2026-06-20 New debounce architecture
2026-06-20 new debounced cleanup
    was out of memory on UIP
2026-06-27 737 Displays Configuration
2026-06-27 throttle
2026-06-27 737 Doc updaate
